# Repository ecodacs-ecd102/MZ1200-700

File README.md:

# MZ1200-700

C104で発表した、MZ-700っぽいMZ-1200 です。

ディレクトリ一覧
- 2732+ExFontSelect
  PCG用フォントROM下駄
- 27512on2332socket
  モニタROMソケットに27512を載せるための下駄
- 2764onCGROMsocket
  PCG無し用フォントROM下駄(2716ソケットに2764を載せる)
- BASIC-PATCH
  BASICパッチ用差分
- BankRAM
  MZ-700互換バンクRAMボード
- ColourBoard
  MZ-700互換カラーRAMボード
- DoubleClock
  倍速基板＋PCG-700互換サブボード
- KBIF
  USBキーボードアダプタ
- MONITOR
  モニタROMパッチ用差分
- MZ-1R12modoki
  MZ-1R12互換バッテリーバックアップS-RAMボード
- PCG
  PCG-700互換メインボード(2種)
- RGB2HDMI
  スキャンコンバータ RGB2HDMI 用のプロファイル
- tools
  細々したツール類

----
 - ROMやBASICの元データは、差分の元バイトを除きここにはありません。各自容易してください。
 - GALのビルドには galette ( https://arbitrary.name/blog/all/galette.html ) が必要です。
 - Z80のアセンブルには、zasm ( https://www.vector.co.jp/soft/dos/prog/se010314.html )をlinux上の MZ-DOS エミュレータ emu2 ( https://github.com/dmsc/emu2 )で動かしています。

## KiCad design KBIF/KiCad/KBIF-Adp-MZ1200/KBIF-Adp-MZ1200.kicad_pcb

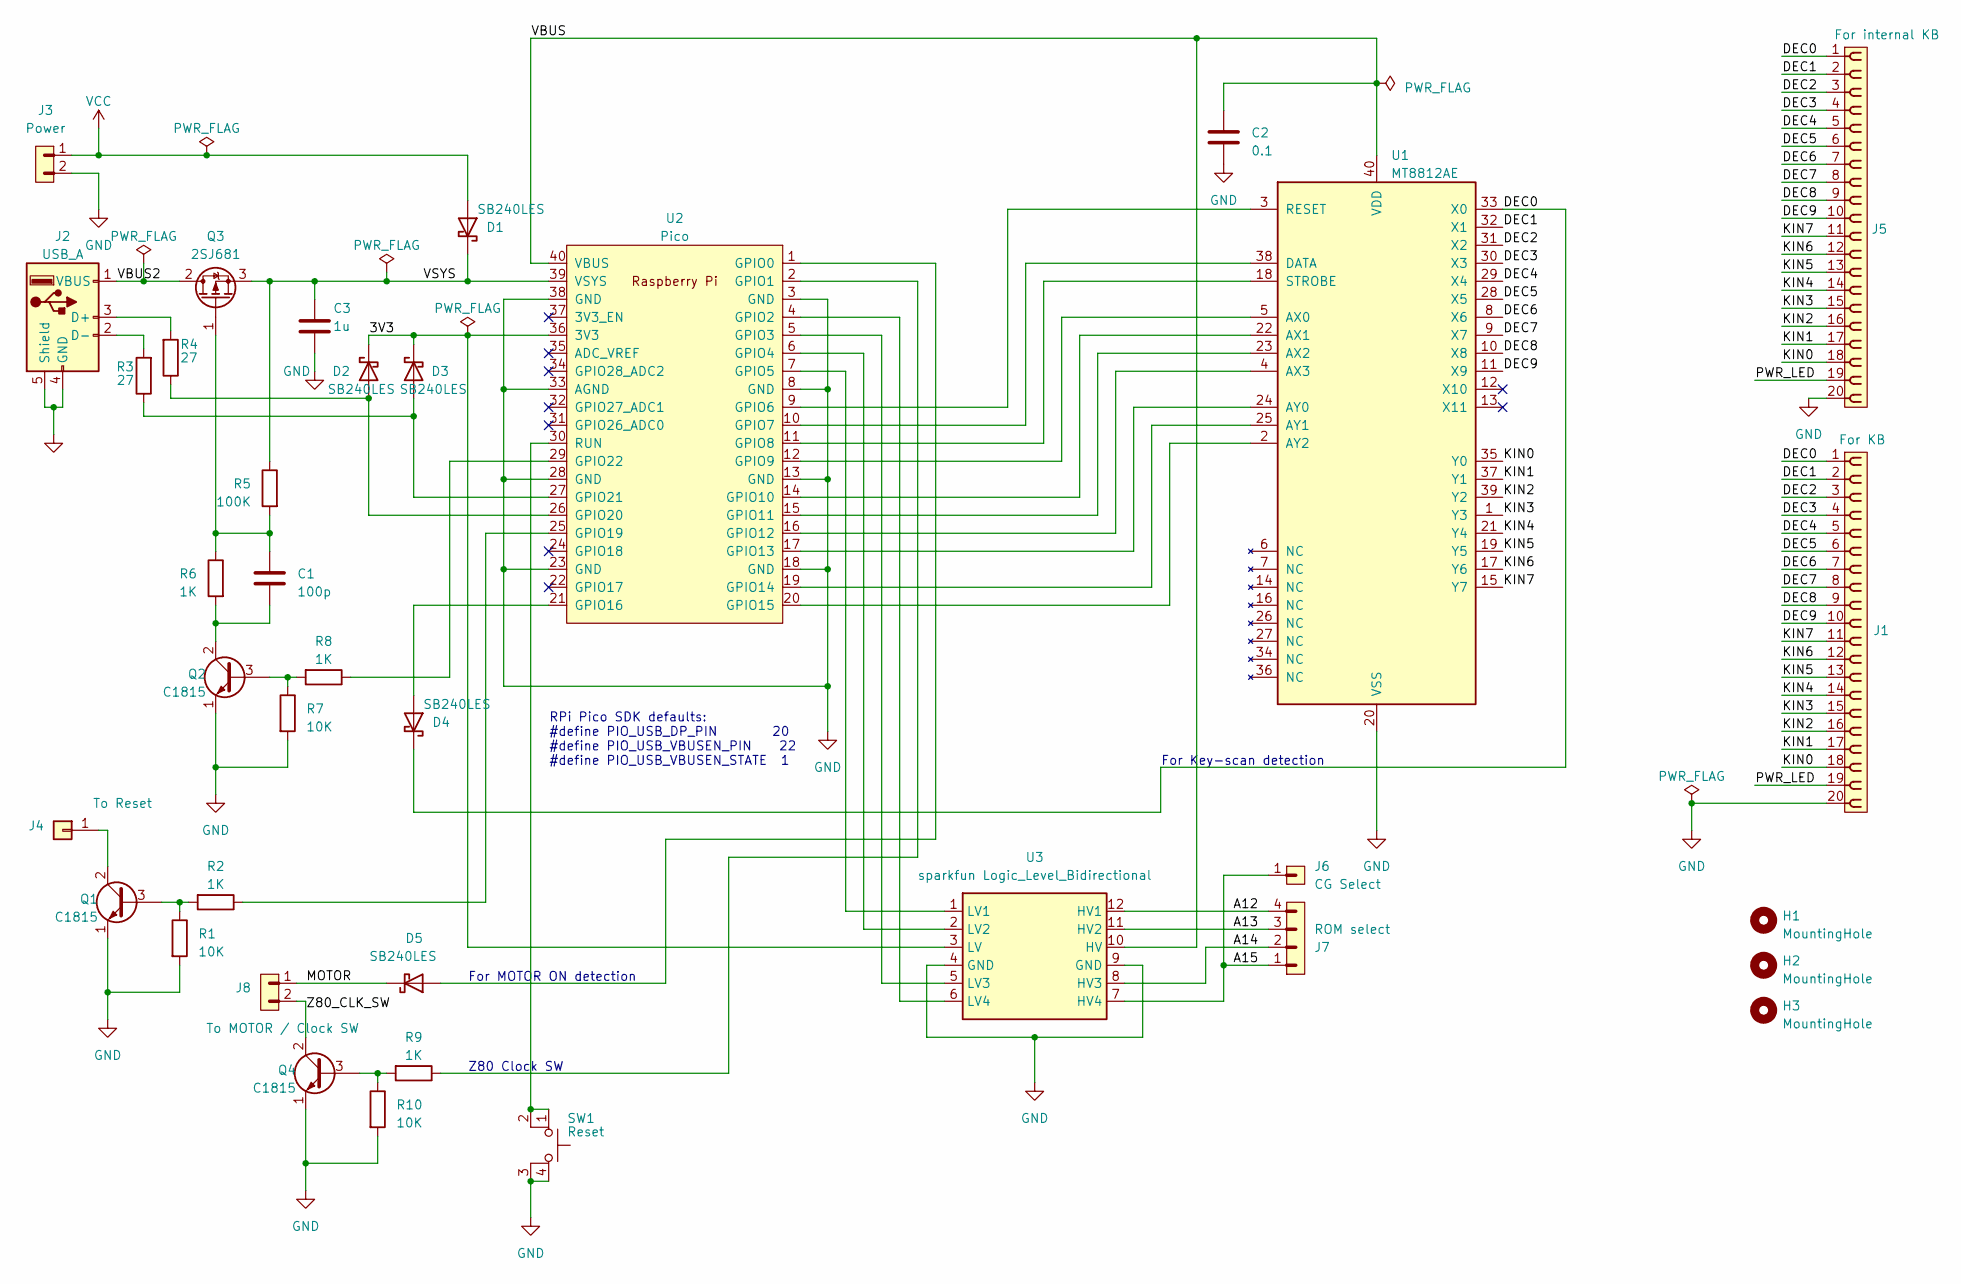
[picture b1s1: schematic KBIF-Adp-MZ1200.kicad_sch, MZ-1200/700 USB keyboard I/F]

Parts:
C1: 100p; LargePad_R_Axial_DIN0204_L3.6mm_D1.6mm_P2.54mm_Vertical
C2: 0.1; LargePad_R_Axial_DIN0204_L3.6mm_D1.6mm_P2.54mm_Vertical
C3: 1u; LargePad_R_Axial_DIN0204_L3.6mm_D1.6mm_P2.54mm_Vertical
D1, D2, D3, D4: SB240LES; D_A-405_P7.62mm_Horizontal_LargePad
D5: SB240LES; D_A-405_P10.16mm_Horizontal
H1, H2, H3: MountingHole; MountingHole_3.2mm_M3
J1: For KB; PinHeader_1x20_P2.54mm_Vertical
J2: USB_A; USB_A_CONNFLY_DS1095-WNR0_LongPad
J3: Power; PinHeader_1x02_P2.54mm_Vertical
J4: To Reset; Pin_D1.1mm_L8.5mm_W2.5mm_FlatFork
J5: For internal KB; PinHeader_1x20_P2.54mm_Vertical
J6: CG Select; PinHeader_1x01_P2.54mm_Vertical
J7: ROM select; PinHeader_1x04_P2.54mm_Vertical
J8: To MOTOR / Clock SW; PinHeader_1x02_P2.54mm_Vertical
Q1, Q2, Q4: C1815; TO-92S_Wide_kao
Q3: 2SJ681; 2-7J2B_Vertical
R1, R7, R10: 10K; LargePad_R_Axial_DIN0207_L6.3mm_D2.5mm_P7.62mm_Horizontal
R2, R6, R8: 1K; LargePad_R_Axial_DIN0207_L6.3mm_D2.5mm_P7.62mm_Horizontal
R3, R4: 27; LargePad_R_Axial_DIN0207_L6.3mm_D2.5mm_P7.62mm_Horizontal
R5: 100K; LargePad_R_Axial_DIN0207_L6.3mm_D2.5mm_P7.62mm_Horizontal
R9: 1K; R_Axial_DIN0207_L6.3mm_D2.5mm_P10.16mm_Horizontal
SW1: Reset; SW_Tactile_Straight_LargePad
U1: MT8812AE; DIP-40_W15.24mm_Socket_LongPads
U2: Pico; raspberry_pi_pico_THT_kao
U3: sparkfun Logic_Level_Bidirectional; DIP-12_W10.16mm_LongPads

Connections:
/3V3: D2.1 (K), D3.1 (K), U2.36 (3V3), U3.3 (LV)
/A12: J7.4, U3.12 (HV1)
/A13: J7.3, U3.11 (HV2)
/A14: J7.2, U3.8 (HV3)
/A15: J6.1, J7.1, U3.7 (HV4)
/DEC0: D4.1 (K), J1.1, J5.1, U1.33 (X0)
/DEC1: J1.2, J5.2, U1.32 (X1)
/DEC2: J1.3, J5.3, U1.31 (X2)
/DEC3: J1.4, J5.4, U1.30 (X3)
/DEC4: J1.5, J5.5, U1.29 (X4)
/DEC5: J1.6, J5.6, U1.28 (X5)
/DEC6: J1.7, J5.7, U1.8 (X6)
/DEC7: J1.8, J5.8, U1.9 (X7)
/DEC8: J1.9, J5.9, U1.10 (X8)
/DEC9: J1.10, J5.10, U1.11 (X9)
/KIN0: J1.18, J5.18, U1.35 (Y0)
/KIN1: J1.17, J5.17, U1.37 (Y1)
/KIN2: J1.16, J5.16, U1.39 (Y2)
/KIN3: J1.15, J5.15, U1.1 (Y3)
/KIN4: J1.14, J5.14, U1.21 (Y4)
/KIN5: J1.13, J5.13, U1.19 (Y5)
/KIN6: J1.12, J5.12, U1.17 (Y6)
/KIN7: J1.11, J5.11, U1.15 (Y7)
/MOTOR: D5.1 (K), J8.1
/PWR_LED: J1.19, J5.19
/VBUS: C2.1, U1.40 (VDD), U2.40 (VBUS), U3.10 (HV)
/VBUS2: J2.1 (VBUS), Q3.2 (D)
/VSYS: C3.1, D1.1 (K), Q3.3 (S), R5.1, U2.39 (VSYS)
/Z80_CLK_SW: J8.2, Q4.2 (C)
GND: C2.2, C3.2, J1.20, J2.4 (GND), J2.5 (Shield), J3.2, J5.20, Q1.1 (E), Q2.1 (E), Q4.1 (E), R1.2, R7.2, R10.2, SW1.3 (K), SW1.4 (A), U1.20 (VSS), U2.3 (GND), U2.8 (GND), U2.13 (GND), U2.18 (GND), U2.23 (GND), U2.28 (GND), U2.33 (AGND), U2.38 (GND), U3.4 (GND), U3.9 (GND)
unnamed: D2.2 (A), R4.1, U2.26 (GPIO20)
unnamed: D3.2 (A), R3.1, U2.27 (GPIO21)
unnamed: D4.2 (A), U2.21 (GPIO16)
unnamed: D5.2 (A), U2.1 (GPIO0)
unnamed: J2.3 (D+), R4.2
unnamed: J2.2 (D-), R3.2
unnamed: J4.1, Q1.2 (C)
unnamed: Q1.3 (B), R1.1, R2.2
unnamed: Q2.3 (B), R7.1, R8.2
unnamed: C1.2, Q2.2 (C), R6.2
unnamed: C1.1, Q3.1 (G), R5.2, R6.1
unnamed: Q4.3 (B), R9.2, R10.1
unnamed: U1.5 (AX0), U2.12 (GPIO9)
unnamed: U1.22 (AX1), U2.14 (GPIO10)
unnamed: U1.23 (AX2), U2.15 (GPIO11)
unnamed: U1.4 (AX3), U2.16 (GPIO12)
unnamed: U1.24 (AY0), U2.17 (GPIO13)
unnamed: U1.25 (AY1), U2.19 (GPIO14)
unnamed: U1.2 (AY2), U2.20 (GPIO15)
unnamed: U1.38 (DATA), U2.10 (GPIO7)
unnamed: U1.3 (RESET), U2.9 (GPIO6)
unnamed: U1.18 (STROBE), U2.11 (GPIO8)
unnamed: R9.1, U2.2 (GPIO1)
unnamed: U2.4 (GPIO2), U3.6 (LV4)
unnamed: U2.5 (GPIO3), U3.5 (LV3)
unnamed: U2.6 (GPIO4), U3.2 (LV2)
unnamed: U2.7 (GPIO5), U3.1 (LV1)
unnamed: R2.1, U2.25 (GPIO19)
unnamed: R8.1, U2.29 (GPIO22)
unnamed: SW1.1, SW1.2, U2.30 (RUN)
VCC: D1.2 (A), J3.1

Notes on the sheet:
RPi Pico SDK defaults: #define PIO_USB_DP_PIN 20 #define PIO_USB_VBUSEN_PIN 22 #define PIO_USB_VBUSEN_STATE 1
Z80 Clock SW
For Key-scan detection
For MOTOR ON detection

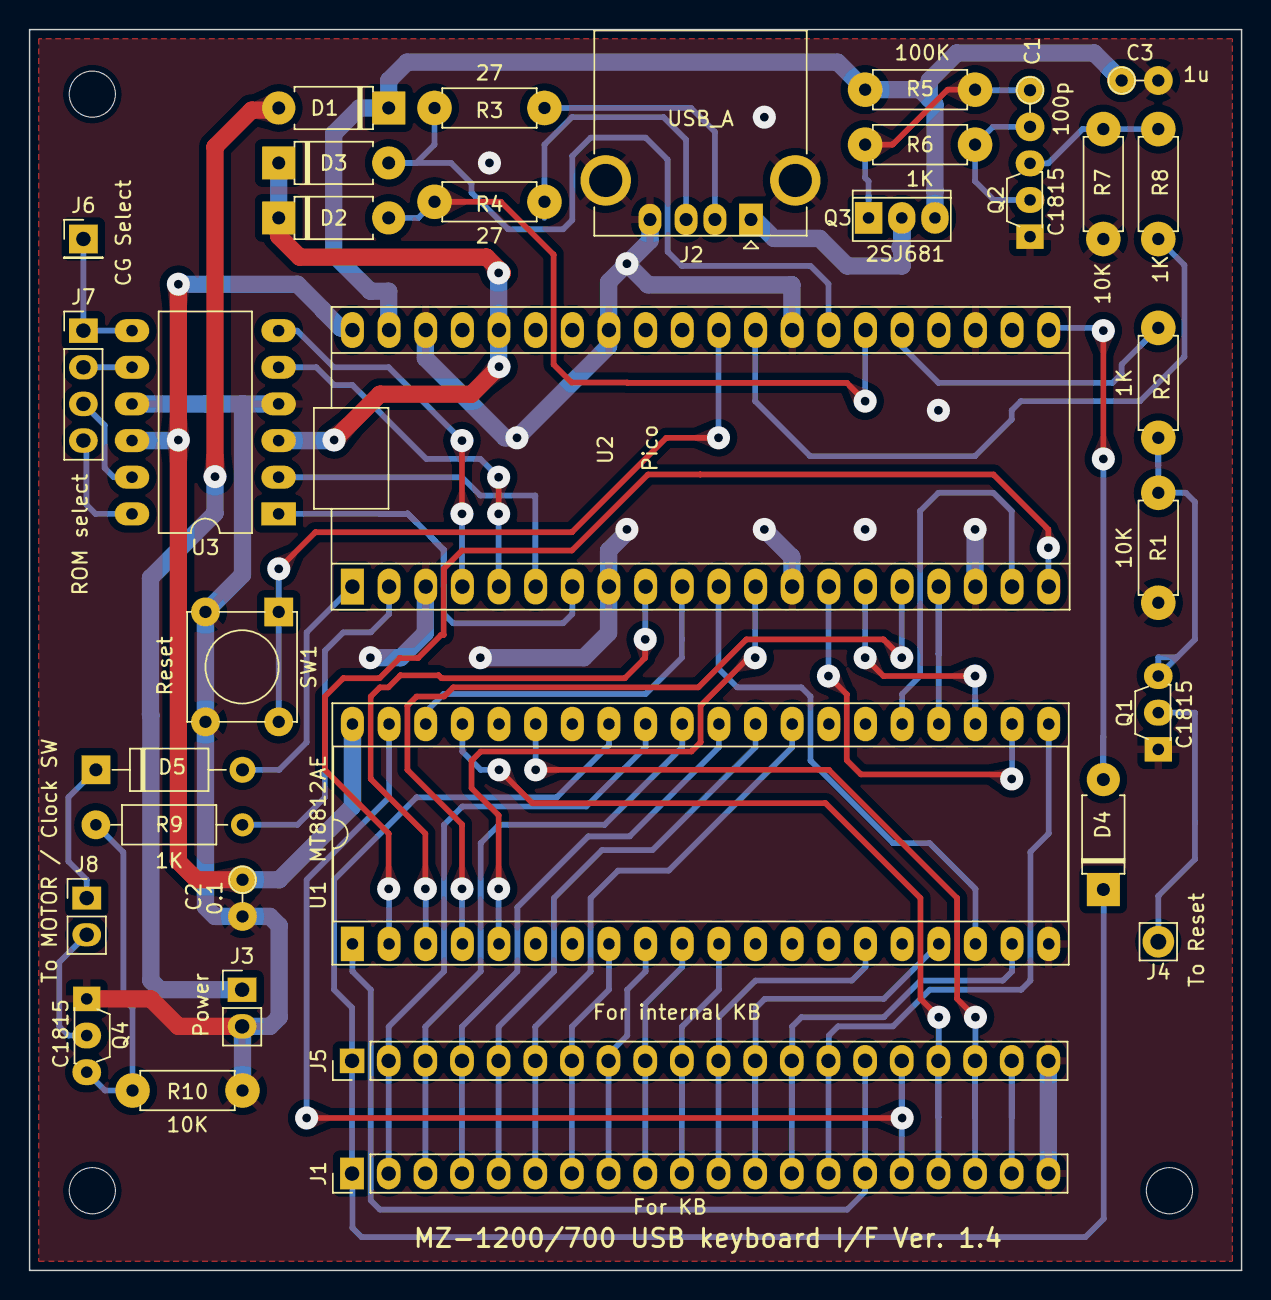
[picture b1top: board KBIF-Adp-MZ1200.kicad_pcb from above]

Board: 2 copper layers, 84.0 x 86.0 mm, 37 parts (0 on the bottom side), 61 nets.

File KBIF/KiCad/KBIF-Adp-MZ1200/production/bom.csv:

Designator,Footprint,Quantity,Value,LCSC Part #
C1,LargePad_R_Axial_DIN0204_L3.6mm_D1.6mm_P2.54mm_Vertical,1,100p,
C2,LargePad_R_Axial_DIN0204_L3.6mm_D1.6mm_P2.54mm_Vertical,1,0.1,
C3,LargePad_R_Axial_DIN0204_L3.6mm_D1.6mm_P2.54mm_Vertical,1,1u,
"D1, D2, D3, D4",D_A-405_P7.62mm_Horizontal_LargePad,4,SB240LES,
D5,D_A-405_P10.16mm_Horizontal,1,SB240LES,
"H1, H2, H3",MountingHole_3.2mm_M3,3,MountingHole,
J1,PinHeader_1x20_P2.54mm_Vertical,1,For KB,
J2,USB_A_CONNFLY_DS1095-WNR0_LongPad,1,USB_A,
J3,PinHeader_1x02_P2.54mm_Vertical,1,Power,
J4,Pin_D1.1mm_L8.5mm_W2.5mm_FlatFork,1,To Reset,
J5,PinHeader_1x20_P2.54mm_Vertical,1,For internal KB,
J6,PinHeader_1x01_P2.54mm_Vertical,1,CG Select,
J7,PinHeader_1x04_P2.54mm_Vertical,1,ROM select,
J8,PinHeader_1x02_P2.54mm_Vertical,1,To MOTOR / Clock SW,
"Q1, Q2, Q4",TO-92S_Wide_kao,3,C1815,
Q3,2-7J2B_Vertical,1,2SJ681,
"R1, R10, R7",LargePad_R_Axial_DIN0207_L6.3mm_D2.5mm_P7.62mm_Horizontal,3,10K,
"R2, R6, R8",LargePad_R_Axial_DIN0207_L6.3mm_D2.5mm_P7.62mm_Horizontal,3,1K,
"R3, R4",LargePad_R_Axial_DIN0207_L6.3mm_D2.5mm_P7.62mm_Horizontal,2,27,
R5,LargePad_R_Axial_DIN0207_L6.3mm_D2.5mm_P7.62mm_Horizontal,1,100K,
R9,R_Axial_DIN0207_L6.3mm_D2.5mm_P10.16mm_Horizontal,1,1K,
SW1,SW_Tactile_Straight_LargePad,1,Reset,
U1,DIP-40_W15.24mm_Socket_LongPads,1,MT8812AE,
U2,raspberry_pi_pico_THT_kao,1,Pico,
U3,DIP-12_W10.16mm_LongPads,1,sparkfun Logic_Level_Bidirectional,

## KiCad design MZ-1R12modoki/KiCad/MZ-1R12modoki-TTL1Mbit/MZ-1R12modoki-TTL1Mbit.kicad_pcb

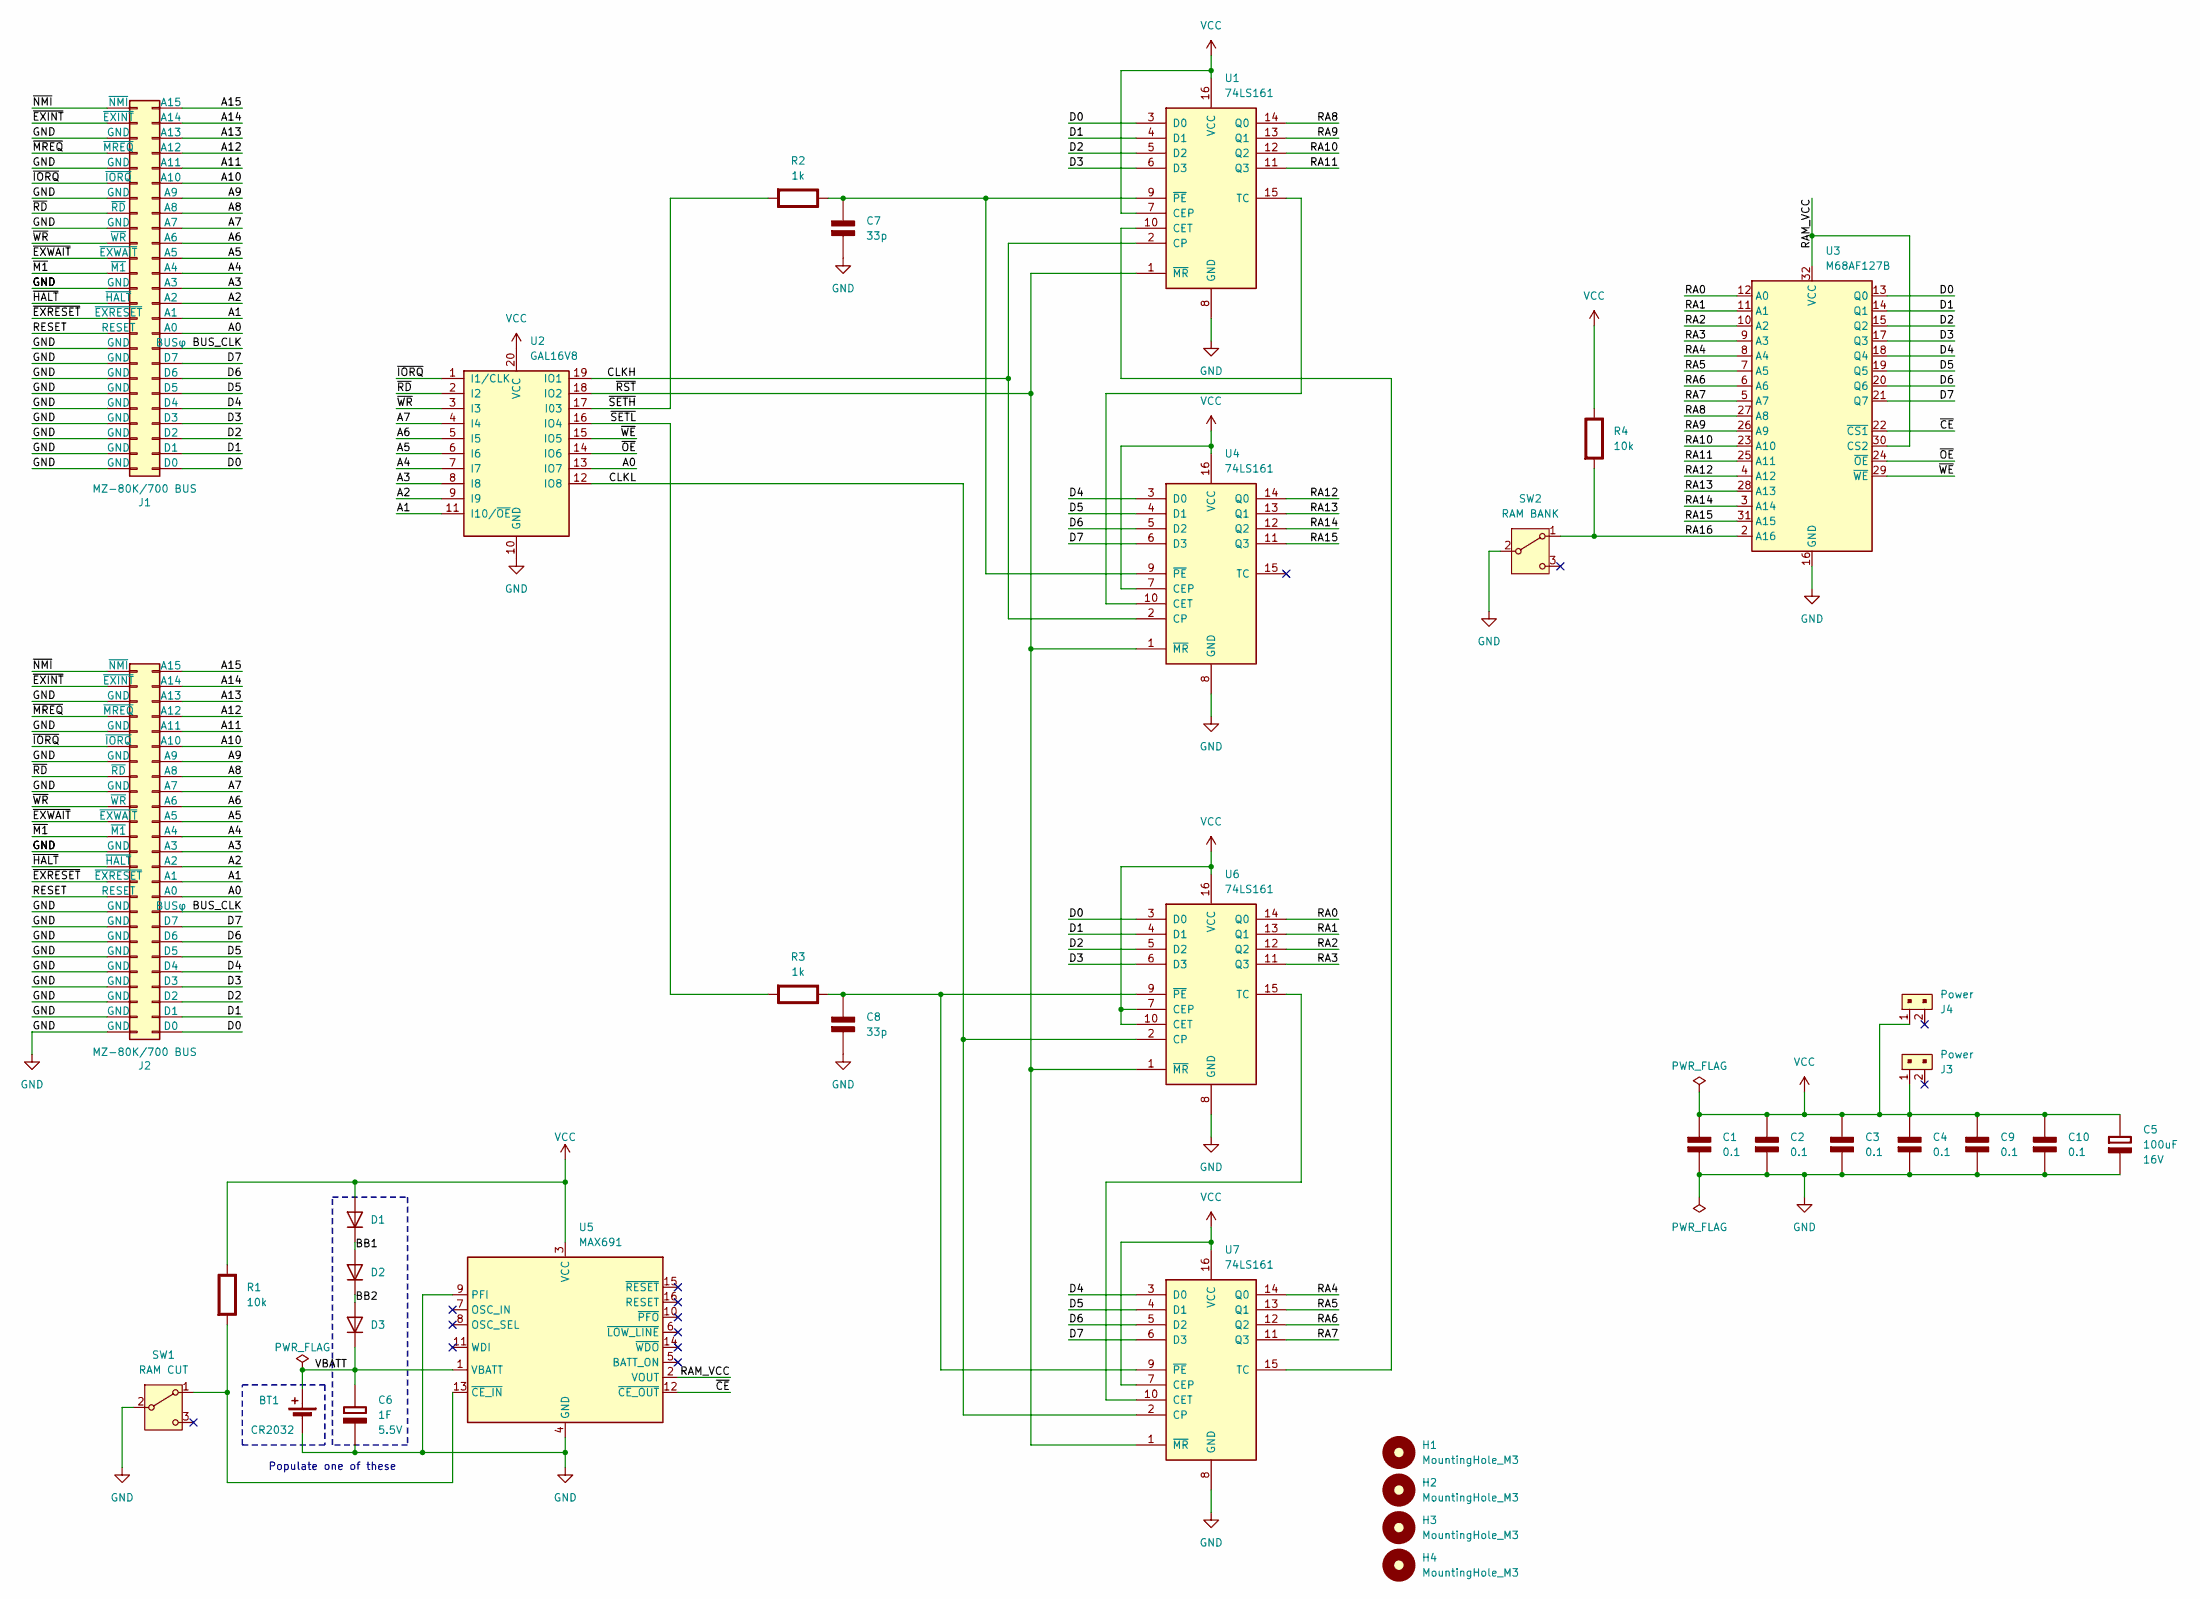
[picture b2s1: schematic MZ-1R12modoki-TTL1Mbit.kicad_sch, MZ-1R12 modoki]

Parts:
BT1: CR2032; Battery_CR2032-AKIZUKI_VERTICAL_HOLDER
C1, C2, C3, C4, C9, C10: 0.1; LargePad_R_Axial_DIN0204_L3.6mm_D1.6mm_P2.54mm_Vertical; Rating V
C5: 100uF; CP_Radial_D7.5mm_P2.50mm; Rating 16V
C6: 1F; DX_5R5VxxxxU_D11.5mm_P5.00mm; Rating 5.5V
C7, C8: 33p; LargePad_R_Axial_DIN0204_L3.6mm_D1.6mm_P2.54mm_Vertical; Rating V
D1, D2, D3: D; D_A-405_P7.62mm_Horizontal_LargePad
H1, H2, H3, H4: MountingHole_M3; MountingHole_3.2mm_M3
J1, J2: MZ-80K/700 BUS; PinSocket_2x25_P2.54mm_Vertical
J3, J4: Power; PinHeader_1x2_P2.5mm_Drill1.1mm; MPN B2B-XH-A(LF)(SN); Digi-Key_PN 455-2247-ND
R1, R4: 10k; LargePad_R_Axial_DIN0207_L6.3mm_D2.5mm_P7.62mm_Horizontal; Rating W
R2, R3: 1k; LargePad_R_Axial_DIN0204_L3.6mm_D1.6mm_P2.54mm_Vertical; Rating W
SW1: RAM CUT; PinHeader_1x03_P2.54mm_Vertical
SW2: RAM BANK; PinHeader_1x03_P2.54mm_Vertical
U1, U4, U6, U7: 74LS161; DIP-16_W7.62mm_Socket_LongPads
U2: GAL16V8; DIP-20_W7.62mm_Socket_LongPads
U3: M68AF127B; SSOP-32_11.305x20.495mm_P1.27mm
U5: MAX691; DIP-16_W7.62mm_Socket_LongPads

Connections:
/A0: J1.31 (A0), J2.31 (A0), U2.13 (IO7)
/A1: J1.29 (A1), J2.29 (A1), U2.11 (I10/~OE)
/A2: J1.27 (A2), J2.27 (A2), U2.9 (I9)
/A3: J1.25 (A3), J2.25 (A3), U2.8 (I8)
/A4: J1.23 (A4), J2.23 (A4), U2.7 (I7)
/A5: J1.21 (A5), J2.21 (A5), U2.6 (I6)
/A6: J1.19 (A6), J2.19 (A6), U2.5 (I5)
/A7: J1.17 (A7), J2.17 (A7), U2.4 (I4)
/A8: J1.15 (A8), J2.15 (A8)
/A9: J1.13 (A9), J2.13 (A9)
/A10: J1.11 (A10), J2.11 (A10)
/A11: J1.9 (A11), J2.9 (A11)
/A12: J1.7 (A12), J2.7 (A12)
/A13: J1.5 (A13), J2.5 (A13)
/A14: J1.3 (A14), J2.3 (A14)
/A15: J1.1 (A15), J2.1 (A15)
/BB1: D1.1 (K), D2.2 (A)
/BB2: D2.1 (K), D3.2 (A)
/BUS_CLK: J1.33 (BUSφ), J2.33 (BUSφ)
/CLKH: U1.2 (CP), U2.19 (IO1), U4.2 (CP)
/CLKL: U2.12 (IO8), U6.2 (CP), U7.2 (CP)
/D0: J1.49 (D0), J2.49 (D0), U1.3 (D0), U3.13 (Q0), U6.3 (D0)
/D1: J1.47 (D1), J2.47 (D1), U1.4 (D1), U3.14 (Q1), U6.4 (D1)
/D2: J1.45 (D2), J2.45 (D2), U1.5 (D2), U3.15 (Q2), U6.5 (D2)
/D3: J1.43 (D3), J2.43 (D3), U1.6 (D3), U3.17 (Q3), U6.6 (D3)
/D4: J1.41 (D4), J2.41 (D4), U3.18 (Q4), U4.3 (D0), U7.3 (D0)
/D5: J1.39 (D5), J2.39 (D5), U3.19 (Q5), U4.4 (D1), U7.4 (D1)
/D6: J1.37 (D6), J2.37 (D6), U3.20 (Q6), U4.5 (D2), U7.5 (D2)
/D7: J1.35 (D7), J2.35 (D7), U3.21 (Q7), U4.6 (D3), U7.6 (D3)
/RA0: U3.12 (A0), U6.14 (Q0)
/RA1: U3.11 (A1), U6.13 (Q1)
/RA2: U3.10 (A2), U6.12 (Q2)
/RA3: U3.9 (A3), U6.11 (Q3)
/RA4: U3.8 (A4), U7.14 (Q0)
/RA5: U3.7 (A5), U7.13 (Q1)
/RA6: U3.6 (A6), U7.12 (Q2)
/RA7: U3.5 (A7), U7.11 (Q3)
/RA8: U1.14 (Q0), U3.27 (A8)
/RA9: U1.13 (Q1), U3.26 (A9)
/RA10: U1.12 (Q2), U3.23 (A10)
/RA11: U1.11 (Q3), U3.25 (A11)
/RA12: U3.4 (A12), U4.14 (Q0)
/RA13: U3.28 (A13), U4.13 (Q1)
/RA14: U3.3 (A14), U4.12 (Q2)
/RA15: U3.31 (A15), U4.11 (Q3)
/RA16: R4.2 (-), SW2.1 (A), U3.2 (A16)
/RAM_VCC: U3.30 (CS2), U3.32 (VCC), U5.2 (VOUT)
/RESET: J1.32 (RESET), J2.32 (RESET)
/VBATT: BT1.1 (+), C6.1 (+), D3.1 (K), U5.1 (VBATT)
/~CE: U3.22 (~CS1), U5.12 (~CE_OUT)
/~EXINT: J1.4 (~EXINT), J2.4 (~EXINT)
/~EXRESET: J1.30 (~EXRESET), J2.30 (~EXRESET)
/~EXWAIT: J1.22 (~EXWAIT), J2.22 (~EXWAIT)
/~HALT: J1.28 (~HALT), J2.28 (~HALT)
/~IORQ: J1.12 (~IORQ), J2.12 (~IORQ), U2.1 (I1/CLK)
/~M1: J1.24 (~M1), J2.24 (~M1)
/~MREQ: J1.8 (~MREQ), J2.8 (~MREQ)
/~NMI: J1.2 (~NMI), J2.2 (~NMI)
/~OE: U2.14 (IO6), U3.24 (~OE)
/~RD: J1.16 (~RD), J2.16 (~RD), U2.2 (I2)
/~RST: U1.1 (~MR), U2.18 (IO2), U4.1 (~MR), U6.1 (~MR), U7.1 (~MR)
/~SETH: R2.2 (-), U2.17 (I03)
/~SETL: R3.2 (-), U2.16 (IO4)
/~WE: U2.15 (IO5), U3.29 (~WE)
/~WR: J1.20 (~WR), J2.20 (~WR), U2.3 (I3)
GND: BT1.2 (-), C1.2 (-), C2.2 (-), C3.2 (-), C4.2 (-), C5.2 (-), C6.2 (-), C7.2 (-), C8.2 (-), C9.2 (-), C10.2 (-), J1.6 (GND), J1.10 (GND), J1.14 (GND), J1.18 (GND), J1.26 (GND), J1.34 (GND), J1.36 (GND), J1.38 (GND), J1.40 (GND), J1.42 (GND), J1.44 (GND), J1.46 (GND), J1.48 (GND), J1.50 (GND), J2.6 (GND), J2.10 (GND), J2.14 (GND), J2.18 (GND), J2.26 (GND), J2.34 (GND), J2.36 (GND), J2.38 (GND), J2.40 (GND), J2.42 (GND), J2.44 (GND), J2.46 (GND), J2.48 (GND), J2.50 (GND), SW1.2 (B), SW2.2 (B), U1.8 (GND), U2.10 (GND), U3.16 (GND), U4.8 (GND), U5.4 (GND), U5.9 (PFI), U6.8 (GND), U7.8 (GND)
unnamed: C7.1 (+), R2.1 (+), U1.9 (~PE), U4.9 (~PE)
unnamed: C8.1 (+), R3.1 (+), U6.9 (~PE), U7.9 (~PE)
unnamed: R1.2 (-), SW1.1 (A), U5.13 (~CE_IN)
unnamed: U1.10 (CET), U7.15 (TC)
unnamed: U1.15 (TC), U4.10 (CET)
unnamed: U6.15 (TC), U7.10 (CET)
VCC: C1.1 (+), C2.1 (+), C3.1 (+), C4.1 (+), C5.1 (+), C9.1 (+), C10.1 (+), D1.2 (A), J3.1, J4.1, R1.1 (+), R4.1 (+), U1.7 (CEP), U1.16 (VCC), U2.20 (VCC), U4.7 (CEP), U4.16 (VCC), U5.3 (VCC), U6.7 (CEP), U6.10 (CET), U6.16 (VCC), U7.7 (CEP), U7.16 (VCC)

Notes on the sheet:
Populate one of these

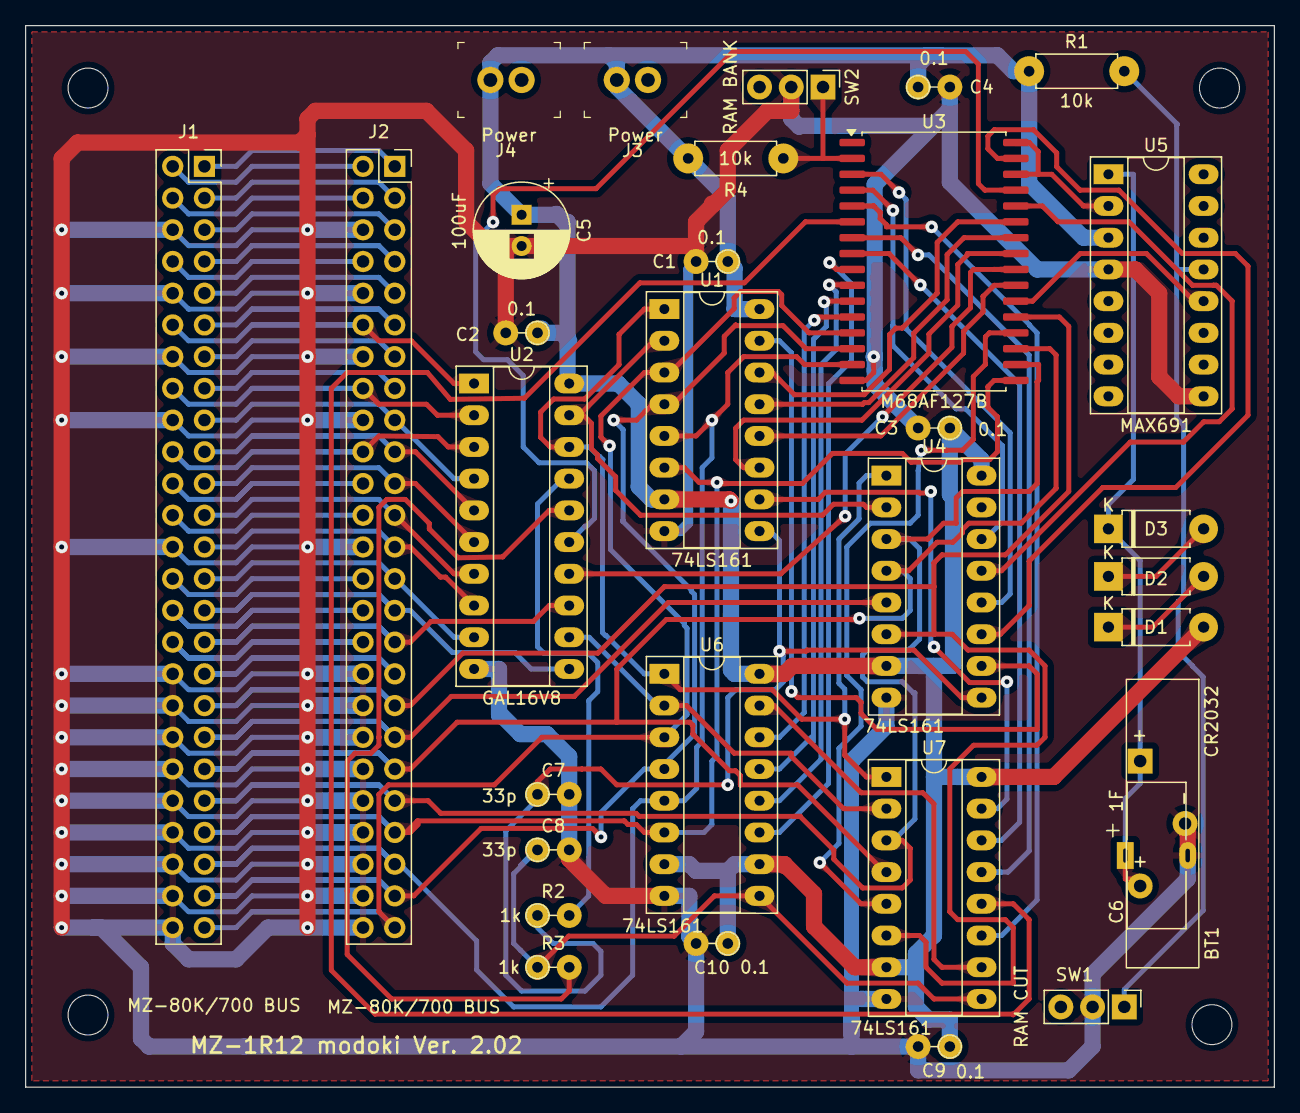
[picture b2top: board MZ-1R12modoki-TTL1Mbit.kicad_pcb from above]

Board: 2 copper layers, 100.0 x 85.0 mm, 35 parts (0 on the bottom side), 73 nets.

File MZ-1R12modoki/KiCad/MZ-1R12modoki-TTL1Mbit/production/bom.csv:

Designator,Footprint,Quantity,Value,LCSC Part #
BT1,Battery_CR2032-AKIZUKI_VERTICAL_HOLDER,1,CR2032,
"C1, C10, C2, C3, C4, C9",LargePad_R_Axial_DIN0204_L3.6mm_D1.6mm_P2.54mm_Vertical,6,0.1,
C5,CP_Radial_D7.5mm_P2.50mm,1,100uF,
C6,DX_5R5VxxxxU_D11.5mm_P5.00mm,1,1F,
"C7, C8",LargePad_R_Axial_DIN0204_L3.6mm_D1.6mm_P2.54mm_Vertical,2,33p,
"D1, D2, D3",D_A-405_P7.62mm_Horizontal_LargePad,3,D,
"H1, H2, H3, H4",MountingHole_3.2mm_M3,4,MountingHole_M3,
"J1, J2",PinSocket_2x25_P2.54mm_Vertical,2,MZ-80K/700 BUS,
"J3, J4",PinHeader_1x2_P2.5mm_Drill1.1mm,2,Power,B2B-XH-A(LF)(SN)
"R1, R4",LargePad_R_Axial_DIN0207_L6.3mm_D2.5mm_P7.62mm_Horizontal,2,10k,
"R2, R3",LargePad_R_Axial_DIN0204_L3.6mm_D1.6mm_P2.54mm_Vertical,2,1k,
SW1,PinHeader_1x03_P2.54mm_Vertical,1,RAM CUT,
SW2,PinHeader_1x03_P2.54mm_Vertical,1,RAM BANK,
"U1, U4, U6, U7",DIP-16_W7.62mm_Socket_LongPads,4,74LS161,
U2,DIP-20_W7.62mm_Socket_LongPads,1,GAL16V8,
U3,SSOP-32_11.305x20.495mm_P1.27mm,1,M68AF127B,
U5,DIP-16_W7.62mm_Socket_LongPads,1,MAX691,

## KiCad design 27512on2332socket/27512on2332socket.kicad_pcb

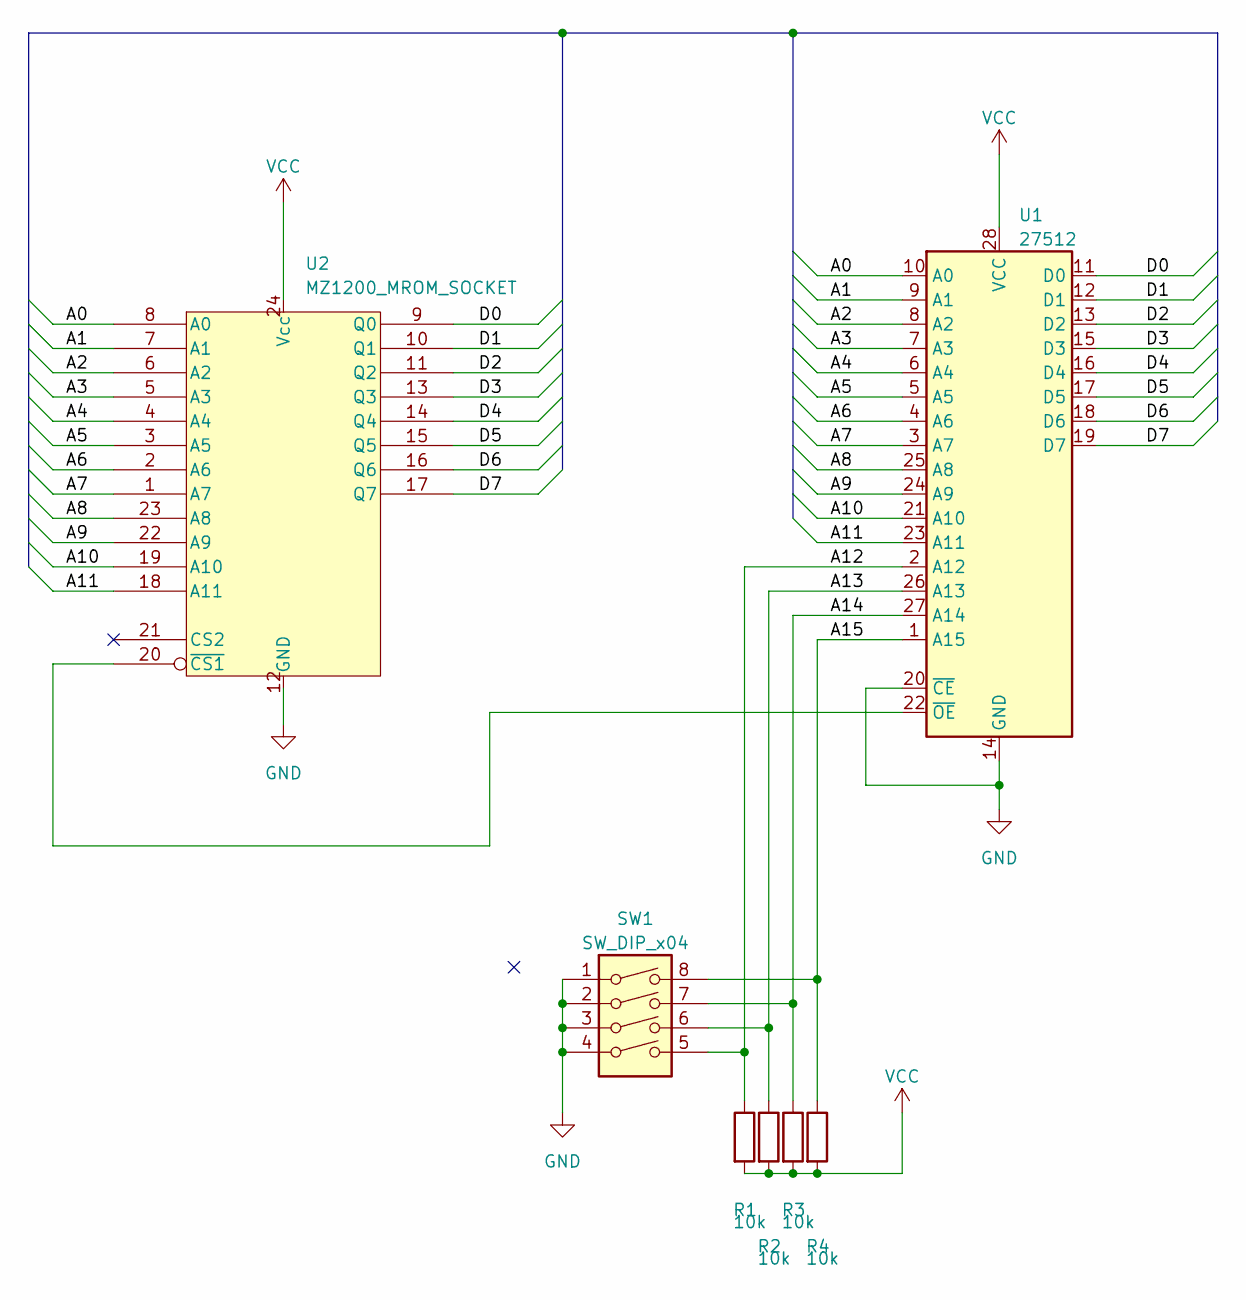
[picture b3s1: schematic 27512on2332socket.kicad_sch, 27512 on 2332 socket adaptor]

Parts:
R1, R2, R3, R4: 10k; R_Axial_DIN0207_L6.3mm_D2.5mm_P7.62mm_Horizontal
SW1: SW_DIP_x04; DIP-8_W7.62mm_Socket_LongPads
U1: 27512; DIP-28_W15.24mm_Socket_LongPads
U2: MZ1200_MROM_SOCKET; DIP-24_W15.24mm_Socket_LongPads

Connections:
/A0: U1.10 (A0), U2.8 (A0)
/A1: U1.9 (A1), U2.7 (A1)
/A2: U1.8 (A2), U2.6 (A2)
/A3: U1.7 (A3), U2.5 (A3)
/A4: U1.6 (A4), U2.4 (A4)
/A5: U1.5 (A5), U2.3 (A5)
/A6: U1.4 (A6), U2.2 (A6)
/A7: U1.3 (A7), U2.1 (A7)
/A8: U1.25 (A8), U2.23 (A8)
/A9: U1.24 (A9), U2.22 (A9)
/A10: U1.21 (A10), U2.19 (A10)
/A11: U1.23 (A11), U2.18 (A11)
/A12: R1.1, SW1.5, U1.2 (A12)
/A13: R2.1, SW1.6, U1.26 (A13)
/A14: R3.1, SW1.7, U1.27 (A14)
/A15: R4.1, SW1.8, U1.1 (A15)
/D0: U1.11 (D0), U2.9 (Q0)
/D1: U1.12 (D1), U2.10 (Q1)
/D2: U1.13 (D2), U2.11 (Q2)
/D3: U1.15 (D3), U2.13 (Q3)
/D4: U1.16 (D4), U2.14 (Q4)
/D5: U1.17 (D5), U2.15 (Q5)
/D6: U1.18 (D6), U2.16 (Q6)
/D7: U1.19 (D7), U2.17 (Q7)
GND: SW1.1, SW1.2, SW1.3, SW1.4, U1.14 (GND), U1.20 (~CE), U2.12 (GND)
unnamed: U1.22 (~OE), U2.20 (~CS1)
VCC: R1.2, R2.2, R3.2, R4.2, U1.28 (VCC), U2.24 (Vcc)

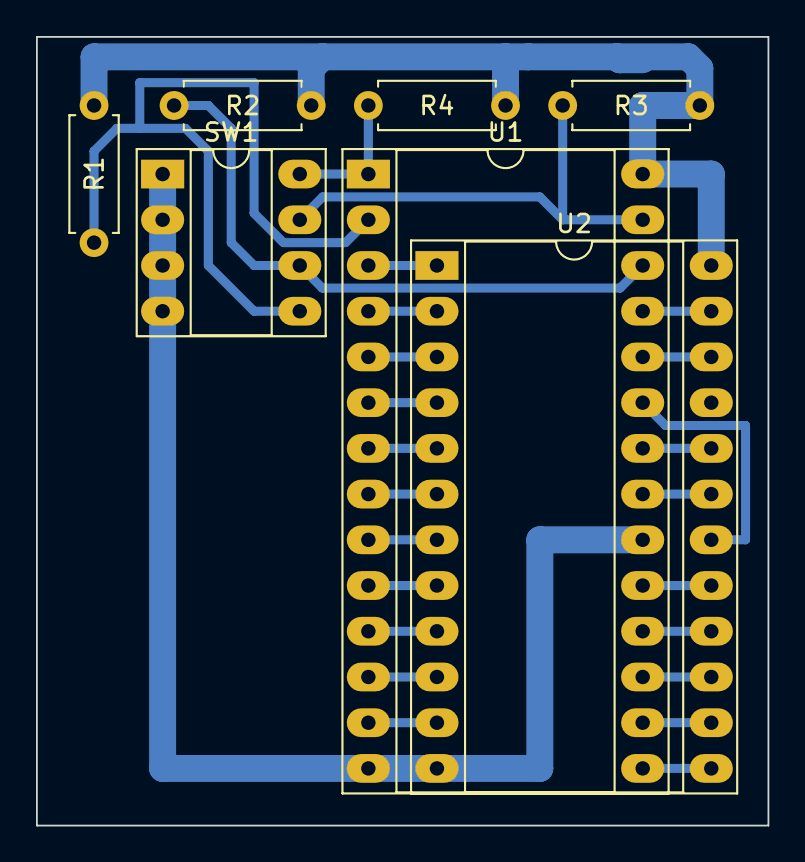
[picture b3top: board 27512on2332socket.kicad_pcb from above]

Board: 2 copper layers, 40.6 x 43.8 mm, 7 parts (0 on the bottom side), 27 nets.

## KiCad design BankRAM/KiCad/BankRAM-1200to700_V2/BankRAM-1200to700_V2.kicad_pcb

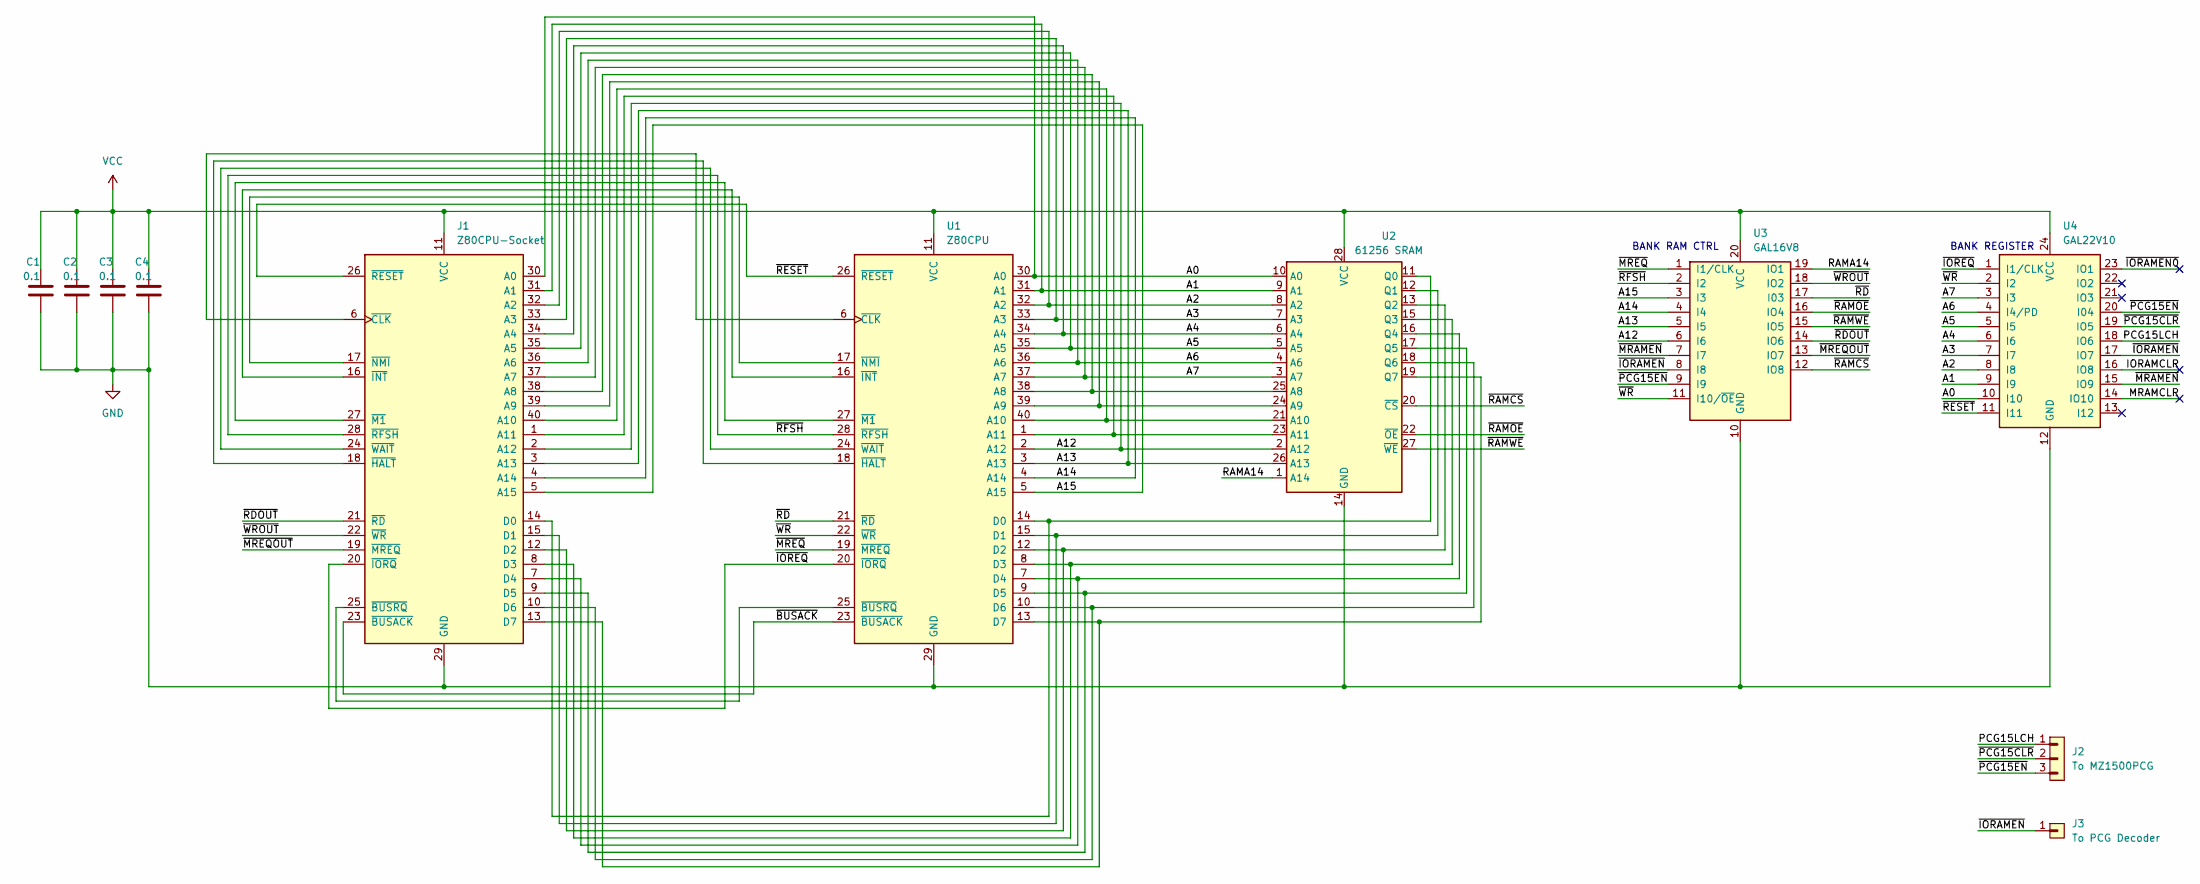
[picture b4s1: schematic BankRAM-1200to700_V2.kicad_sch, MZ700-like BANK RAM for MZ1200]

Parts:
C1, C2, C3, C4: 0.1; LargePad_R_Axial_DIN0204_L3.6mm_D1.6mm_P2.54mm_Vertical
J1: Z80CPU-Socket; DIP-40_W15.24mm_Socket_LongPads
J2: To MZ1500PCG; PinHeader_1x03_P2.54mm_Vertical
J3: To PCG Decoder; PinHeader_1x01_P2.54mm_Vertical
U1: Z80CPU; DIP-40_W15.24mm_Socket_LongPads
U2: 61256 SRAM; DIP-28_W15.24mm_Socket_LongPads
U3: GAL16V8; DIP-20_W7.62mm_Socket_LongPads
U4: GAL22V10; DIP-24_W7.62mm_Socket_LongPads

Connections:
/A0: J1.30 (A0), U1.30 (A0), U2.10 (A0), U4.10 (I10)
/A1: J1.31 (A1), U1.31 (A1), U2.9 (A1), U4.9 (I9)
/A2: J1.32 (A2), U1.32 (A2), U2.8 (A2), U4.8 (I8)
/A3: J1.33 (A3), U1.33 (A3), U2.7 (A3), U4.7 (I7)
/A4: J1.34 (A4), U1.34 (A4), U2.6 (A4), U4.6 (I6)
/A5: J1.35 (A5), U1.35 (A5), U2.5 (A5), U4.5 (I5)
/A6: J1.36 (A6), U1.36 (A6), U2.4 (A6), U4.4 (I4/PD)
/A7: J1.37 (A7), U1.37 (A7), U2.3 (A7), U4.3 (I3)
/A12: J1.2 (A12), U1.2 (A12), U2.2 (A12), U3.6 (I6)
/A13: J1.3 (A13), U1.3 (A13), U2.26 (A13), U3.5 (I5)
/A14: J1.4 (A14), U1.4 (A14), U3.4 (I4)
/A15: J1.5 (A15), U1.5 (A15), U3.3 (I3)
/IORAMCLR: U4.16 (IO8)
/MRAMCLR: U4.14 (IO10)
/PCG15LCH: J2.1, U4.18 (IO6)
/RAMA14: U2.1 (A14), U3.19 (IO1)
/~BUSACK: J1.23 (~BUSACK), U1.23 (~BUSACK)
/~IORAMEN0: U4.23 (IO1)
/~IORAMEN: J3.1, U3.8 (I8), U4.17 (IO7)
/~IOREQ: J1.20 (~IORQ), U1.20 (~IORQ), U4.1 (I1/CLK)
/~MRAMEN: U3.7 (I7), U4.15 (IO9)
/~MREQOUT: J1.19 (~MREQ), U3.13 (IO7)
/~MREQ: U1.19 (~MREQ), U3.1 (I1/CLK)
/~PCG15CLR: J2.2, U4.19 (IO5)
/~PCG15EN: J2.3, U3.9 (I9), U4.20 (I04)
/~RAMCS: U2.20 (~CS), U3.12 (IO8)
/~RAMOE: U2.22 (~OE), U3.16 (IO4)
/~RAMWE: U2.27 (~WE), U3.15 (IO5)
/~RDOUT: J1.21 (~RD), U3.14 (IO6)
/~RD: U1.21 (~RD), U3.17 (I03)
/~RESET: J1.26 (~RESET), U1.26 (~RESET), U4.11 (I11)
/~RFSH: J1.28 (~RFSH), U1.28 (~RFSH), U3.2 (I2)
/~WROUT: J1.22 (~WR), U3.18 (IO2)
/~WR: U1.22 (~WR), U3.11 (I10/~OE), U4.2 (I2)
GND: C1.2, C2.2, C3.2, C4.2, J1.29 (GND), U1.29 (GND), U2.14 (GND), U3.10 (GND), U4.12 (GND)
unnamed: J1.38 (A8), U1.38 (A8), U2.25 (A8)
unnamed: J1.39 (A9), U1.39 (A9), U2.24 (A9)
unnamed: J1.40 (A10), U1.40 (A10), U2.21 (A10)
unnamed: J1.1 (A11), U1.1 (A11), U2.23 (A11)
unnamed: J1.14 (D0), U1.14 (D0), U2.11 (Q0)
unnamed: J1.15 (D1), U1.15 (D1), U2.12 (Q1)
unnamed: J1.12 (D2), U1.12 (D2), U2.13 (Q2)
unnamed: J1.8 (D3), U1.8 (D3), U2.15 (Q3)
unnamed: J1.7 (D4), U1.7 (D4), U2.16 (Q4)
unnamed: J1.9 (D5), U1.9 (D5), U2.17 (Q5)
unnamed: J1.10 (D6), U1.10 (D6), U2.18 (Q6)
unnamed: J1.13 (D7), U1.13 (D7), U2.19 (Q7)
unnamed: J1.25 (~BUSRQ), U1.25 (~BUSRQ)
unnamed: J1.6 (~CLK), U1.6 (~CLK)
unnamed: J1.18 (~HALT), U1.18 (~HALT)
unnamed: J1.16 (~INT), U1.16 (~INT)
unnamed: J1.27 (~M1), U1.27 (~M1)
unnamed: J1.17 (~NMI), U1.17 (~NMI)
unnamed: J1.24 (~WAIT), U1.24 (~WAIT)
VCC: C1.1, C2.1, C3.1, C4.1, J1.11 (VCC), U1.11 (VCC), U2.28 (VCC), U3.20 (VCC), U4.24 (VCC)

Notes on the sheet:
BANK REGISTER
BANK RAM CTRL
